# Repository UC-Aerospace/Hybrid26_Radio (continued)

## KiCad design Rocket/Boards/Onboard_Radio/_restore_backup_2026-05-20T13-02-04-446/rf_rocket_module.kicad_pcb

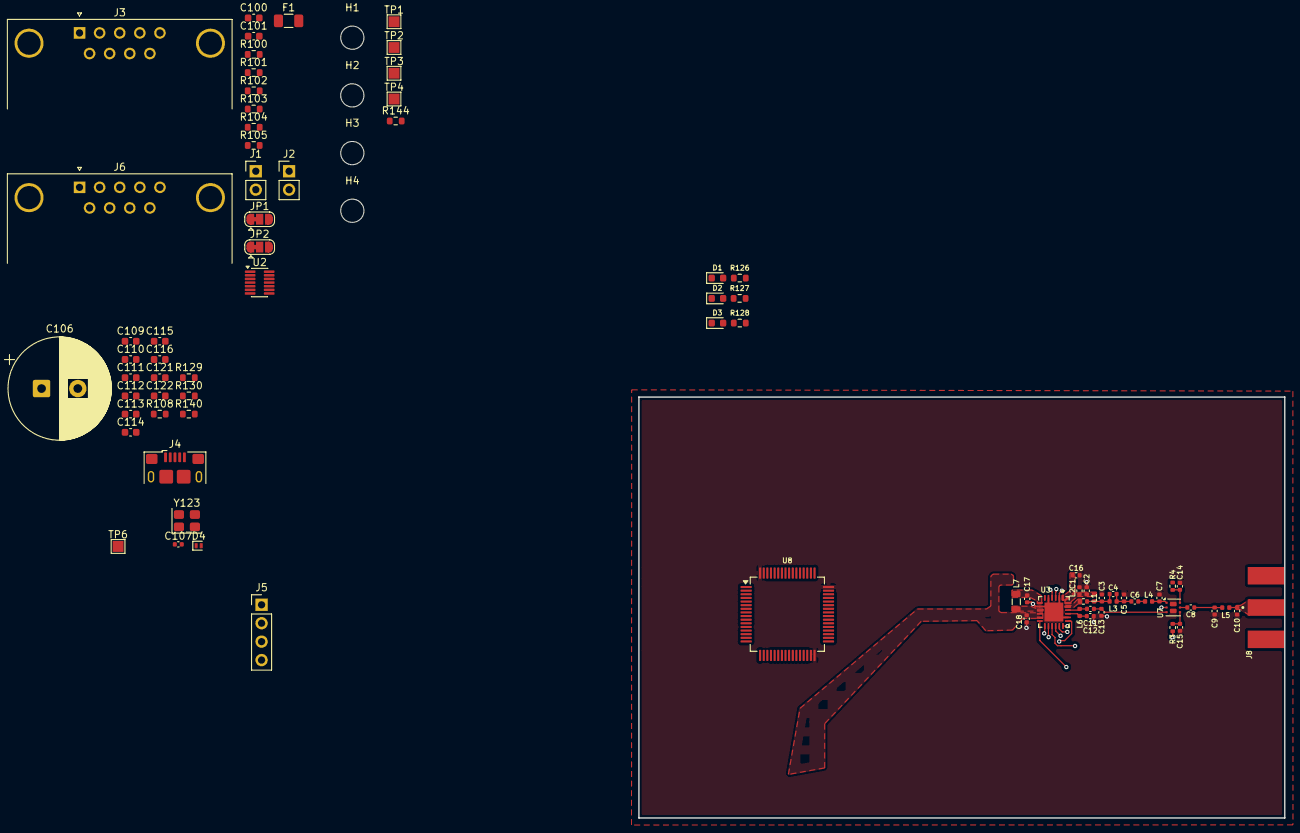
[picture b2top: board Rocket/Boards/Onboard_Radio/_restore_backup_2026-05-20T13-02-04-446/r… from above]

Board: 4 copper layers, 89.0 x 58.0 mm, 83 parts (0 on the bottom side), 53 nets.

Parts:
C1, C2: 47pF; C_0402_1005Metric
C3, C13: ???; C_0402_1005Metric
C4: 3.0pF; C_0402_1005Metric
C5: 5.6pF; C_0402_1005Metric
C6, C8: 39pF; C_0402_1005Metric
C7, C12: 1.8pF; C_0402_1005Metric
C9, C10: 3.3pF; C_0402_1005Metric
C11: 2.4pF; C_0402_1005Metric
C14, C15: 1nF; C_0402_1005Metric
C16: 1uF; C_0402_1005Metric
C17: 470nF; C_0402_1005Metric
C18: 100nF; C_0402_1005Metric
C100, C101, C109, C110, C113, C115: 100nF; C_0603_1608Metric
C106: 100m; CP_Radial_D14.0mm_P5.00mm
C107: 100n; C_0402_1005Metric
C111, C112, C114, C116: 4.7uF; C_0603_1608Metric
C121, C122: 27pF; C_0603_1608Metric
D1: LED_Y; LED_0603_1608Metric
D2: LED_G; LED_0603_1608Metric
D3: LED_R; LED_0603_1608Metric
D4: D_Schottky; D_SOD-882
F1: 5A; Fuse_1206_3216Metric
H1, H2, H3, H4: MountingHole; MountingHole_3.2mm_M3
J1: CAN1_T; PinHeader_1x02_P2.54mm_Vertical
J2: CAN2_T; PinHeader_1x02_P2.54mm_Vertical
J3, J6: DB9 Microfit; DSUB-9_Pins_Horizontal_P2.77x2.84mm_EdgePinOffset7.70mm_Hou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
J4: USB_B_Micro; USB_Micro-B_Amphenol_10118193-0001LF_Horizontal
J5: SWD JST PH; PinHeader_1x04_P2.54mm_Vertical
J8: RFIO SMA; JOHNSON_142-0701-841
JP1, JP2: CH SEL; SolderJumper-3_P1.3mm_Bridged12_RoundedPad1.0x1.5mm
L1: 47nH; L_0402_1005Metric
L2: 0R; R_0402_1005Metric
L3: 2.5nH; L_0402_1005Metric
L4: 4.7nH; L_0402_1005Metric
L5: 9.1nH; L_0402_1005Metric
L6: 15nH; L_0402_1005Metric
L7: 15uH; L_0805_2012Metric
R3, R4: 100R; R_0402_1005Metric
R100, R101, R102, R103: 100K; R_0603_1608Metric
R104, R105: 120R; R_0603_1608Metric
R108: 33R; R_0603_1608Metric
R126: 549R; R_0603_1608Metric
R127, R128: 220R; R_0603_1608Metric
R129: R; R_0603_1608Metric
R130, R140: 27R; R_0603_1608Metric
R144: 0R; R_0603_1608Metric
TP1: 7V4; TestPoint_Pad_1.5x1.5mm
TP2: 5V; TestPoint_Pad_1.5x1.5mm
TP3: 3V3; TestPoint_Pad_1.5x1.5mm
TP4: GND; TestPoint_Pad_1.5x1.5mm
TP6: RTC_CAP; TestPoint_Pad_1.5x1.5mm
U2: TCAN1046; Texas_DYY0014A_TSOT-23-14
U3: SX1262; QFN-24-1EP_4x4mm_P0.5mm_EP2.6x2.6mm
U7: PE4259 RF Switch; Vishay_PowerPAK_SC70-6L_Dual
U8: STM32H562RGT6; LQFP-64_10x10mm_P0.5mm
Y123: 12MHz; Crystal_SMD_Abracon_ABM8G-4Pin_3.2x2.5mm

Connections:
+3V3: C101.1, C109.1, C110.1, C111.1, C112.1, C113.1, C114.1, C115.1, C116.1, R100.1, R101.2, R102.2, R103.1, R108.2, R129.1, TP3.1 (1_1), U2.3 (VCC)
+5V: C100.1, TP2.1 (1_1), U2.11 (VIO)
+7V4: F1.1, R126.1, R144.2, TP1.1 (1_1)
/CAN_Termination/CAN1_RX: U2.4 (RXD1), U8.61 (PB8)
/CAN_Termination/CAN1_TX: U2.1 (TXD1), U8.59 (PB7)
/CAN_Termination/CANH: JP1.2 (C), U2.13 (CANH1)
/CAN_Termination/CANH1: J1.1, J3.6, J6.6, JP1.1 (A)
/CAN_Termination/CANH2: J3.8, J6.8, JP1.3 (B), R105.1
/CAN_Termination/CANL: JP2.2 (C), U2.12 (CANL1)
/CAN_Termination/CANL1: J3.7, J6.7, JP2.1 (A), R104.2
/CAN_Termination/CANL2: J2.1, J3.9, J6.9, JP2.3 (B)
/LoRav2/DIO2: R3.1, U3.12 (DIO2)
/MCU/LED1: R127.1, U8.9 (PC1)
/MCU/LED2: R128.1, U8.10 (PC2)
/MCU/NRST: J5.4, R129.2, U8.7 (NRST)
/MCU/SWCLK: J5.1, U8.46 (PA13(JTMS)
/MCU/SWDIO: J5.3, U8.49 (PA14(JTCK)
/MCU/USB_D+: J4.3 (D+), R140.2
/MCU/USB_D-: J4.2 (D-), R130.1
GND: C1.2, C2.2, C3.2, C5.2, C7.2, C9.2, C10.2, C12.2, C13.2, C14.2, C15.2, C16.2, C17.2, C18.2, C100.2, C101.2, C106.2, C107.2, C109.2, C110.2, C111.2, C112.2, C113.2, C114.2, C115.2, C116.2, C121.1, C122.2, D1.1 (K), D2.1 (K), D3.1 (K), J3.2, J3.4, J4.5 (GND), J5.2, J6.2, J6.4, TP4.1 (1_1), U2.2 (GND), U2.5 (GND), U3.2 (GND), U3.5 (GND), U3.8 (GND), U3.20 (GND), U3.25 (GND), U7.2 (GND), U8.12 (VSSA), U8.18 (VSS), U8.19 (VDD), U8.31 (VSS), U8.32 (VDD), U8.47 (VSS), U8.48 (VDD), U8.63 (VSS), U8.64 (VDD)
unnamed: C3.1, C4.1, L1.1, L2.2, L3.1
unnamed: C4.2, C5.1, C6.1, L3.2
unnamed: C6.2, L4.1
unnamed: C8.2, C9.1, L5.1
unnamed: D1.2 (A), R126.2
unnamed: D2.2 (A), R127.2
unnamed: D3.2 (A), R128.2
unnamed: D4.2 (A), R108.1
unnamed: C106.1, C107.1, D4.1 (K), TP6.1 (1_1), U8.1 (VBAT)
unnamed: F1.2, J3.1, J3.5, J6.1, J6.5
unnamed: J1.2, R104.1
unnamed: J2.2, R105.2
unnamed: C10.1, J8.1 (In_1), L5.2
unnamed: R102.1, U2.7 (RXD2)
unnamed: R100.2, U2.14 (STB1)
unnamed: R103.2, U2.8 (STB2)
unnamed: R101.1, U2.6 (TXD2)
unnamed: L7.1, U3.9 (DCC_SW)
unnamed: C11.1, L6.2, U3.22 (RFI_N)
unnamed: C12.1, L6.1, U3.21 (RFI_P)
unnamed: L2.1, U3.23 (RFO)
unnamed: C17.1, L7.2, U3.7 (VREG)
unnamed: C1.1, C2.1, L1.2, U3.24 (VR_PA)
unnamed: C15.1, R3.2, U7.4 (CTRL)
unnamed: C8.1, U7.5 (RFC)
unnamed: C7.1, L4.2, U7.1 (RF_1)
unnamed: C11.2, C13.1, U7.3 (RF_2)
unnamed: C14.1, R4.2, U7.6 (VDD)
unnamed: R130.2, U8.44 (PA11)
unnamed: R140.1, U8.45 (PA12)
unnamed: C121.2, U8.5 (PH0), Y123.2
unnamed: C122.1, U8.6 (PH1), Y123.1
VDD_RADIO: C16.1, C18.1, U3.1 (VDD_IN), U3.10 (VBAT), U3.11 (VBAT_IO)

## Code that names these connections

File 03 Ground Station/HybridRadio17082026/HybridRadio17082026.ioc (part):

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Mcu.Name=STM32H562RGTx
Mcu.Package=LQFP64
Mcu.UserName=STM32H562RGTx
PA0.Mode=Asynchronous
PA0.Signal=UART4_TX
PA1.Mode=Asynchronous
PA1.Signal=UART4_RX
PA11.Mode=Device
PA11.Signal=USB_DM
PA12.Mode=Device
PA12.Signal=USB_DP
PA2.GPIOParameters=GPIO_Label
PA2.GPIO_Label=ANT_SW
PA2.Signal=GPIO_Output
PA4.GPIOParameters=GPIO_Label
PA4.GPIO_Label=SX1262_CS
PA4.Signal=GPIO_Output
PA5.Mode=Full_Duplex_Master
PA5.Signal=SPI1_SCK
PA6.Mode=Full_Duplex_Master
PA6.Signal=SPI1_MISO
PA7.Mode=Full_Duplex_Master
PA7.Signal=SPI1_MOSI
PB0.GPIOParameters=GPIO_Label
PB0.GPIO_Label=SX1262_RESET
PB0.Signal=GPIO_Output
PB1.GPIOParameters=GPIO_Label
PB1.GPIO_Label=SX1262_BUSY
PB1.Signal=GPIO_Input
PB2.GPIOParameters=GPIO_Label
PB2.GPIO_Label=SX1262_DIO1
PB2.Signal=GPIO_Input
PC10.GPIOParameters=GPIO_Label
PC10.GPIO_Label=LED2
PC10.Signal=GPIO_Output
PC11.GPIOParameters=GPIO_Label
PC11.GPIO_Label=LED1
PC11.Signal=GPIO_Output
PC13.GPIOParameters=GPIO_Label
PC13.GPIO_Label=LDO_3V3A_EN
PC13.Signal=GPIO_Output
PC14-OSC32_IN(OSC32_IN).GPIOParameters=GPIO_Label
PC14-OSC32_IN(OSC32_IN).GPIO_Label=LDO_3V3D_EN
PC14-OSC32_IN(OSC32_IN).Signal=GPIO_Output
PH0-OSC_IN(PH0).Mode=HSE-External-Oscillator
PH0-OSC_IN(PH0).Signal=RCC_OSC_IN
PH1-OSC_OUT(PH1).Mode=HSE-External-Oscillator
PH1-OSC_OUT(PH1).Signal=RCC_OSC_OUT
RCC.HSE_VALUE=12000000
RCC.SYSCLKFreq_VALUE=32000000
board=custom

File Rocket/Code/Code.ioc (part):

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Mcu.Name=STM32H562RGTx
Mcu.Package=LQFP64
Mcu.UserName=STM32H562RGTx
PA11.Mode=Device
PA11.Signal=USB_DM
PA12.Mode=Device
PA12.Signal=USB_DP
PA13(JTMS/SWDIO).Mode=Serial_Wire
PA13(JTMS/SWDIO).Signal=DEBUG_JTMS-SWDIO
PA14(JTCK/SWCLK).Mode=Serial_Wire
PA14(JTCK/SWCLK).Signal=DEBUG_JTCK-SWCLK
PA4.GPIOParameters=PinState,GPIO_Label
PA4.GPIO_Label=SX1262_CS
PA4.PinState=GPIO_PIN_SET
PA4.Signal=GPIO_Output
PA5.Mode=Full_Duplex_Master
PA5.Signal=SPI1_SCK
PA6.Mode=Full_Duplex_Master
PA6.Signal=SPI1_MISO
PA7.Mode=Full_Duplex_Master
PA7.Signal=SPI1_MOSI
PB0.GPIOParameters=PinState,GPIO_Label
PB0.GPIO_Label=SX1262_RESET
PB0.PinState=GPIO_PIN_SET
PB0.Signal=GPIO_Output
PB1.GPIOParameters=GPIO_Label
PB1.GPIO_Label=SX1262_BUSY
PB1.Signal=GPIO_Output
PB2.GPIOParameters=GPIO_Label,GPIO_ModeDefaultEXTI
PB2.GPIO_Label=SX1262_DIO1
PB2.GPIO_ModeDefaultEXTI=GPIO_MODE_IT_RISING
PB2.Signal=GPXTI2
PB7.Mode=FDCAN_Activate
PB7.Signal=FDCAN1_TX
PB8.Mode=FDCAN_Activate
PB8.Signal=FDCAN1_RX
PC1.GPIOParameters=GPIO_Label
PC1.GPIO_Label=LED1
PC1.Signal=GPIO_Output
PC2.GPIOParameters=GPIO_Label
PC2.GPIO_Label=LED2
PC2.Signal=GPIO_Output
PH0-OSC_IN(PH0).Mode=HSE-External-Oscillator
PH0-OSC_IN(PH0).Signal=RCC_OSC_IN
PH1-OSC_OUT(PH1).Mode=HSE-External-Oscillator
PH1-OSC_OUT(PH1).Signal=RCC_OSC_OUT
RCC.HSE_VALUE=12000000
RCC.SYSCLKFreq_VALUE=32000000
board=custom

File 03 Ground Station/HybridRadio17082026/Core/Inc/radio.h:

/*
 * sx1262.h
 *
 * Minimal SX1262 LoRa driver for the "Onboard Radio" board.
 * Configures the radio for LoRa, -9 dBm output (the lowest the physical
 * SX1262 PA supports), 915 MHz, SF7/BW125/CR4:5, and repeatedly
 * transmits a test packet.
 *
 * All opcodes, parameter encodings, and register/pin behaviour referenced
 * against: Semtech DS.SX1261-2.W.APP Rev 1.1 ("the datasheet" in comments).
 *
 * ---- Wiring assumptions (must match your CubeMX Pinout labels) ----
 * SPI1            -> SCK/MISO/MOSI to the SX1262 (CPOL=0, CPHA=0, per
 *                    datasheet Section 8.2, p.48). NSS is software-controlled
 *                    (NOT SPI1's hardware NSS) so we can hold it low/high
 *                    exactly when the datasheet's command framing needs it.
 * SX1262_CS       -> GPIO output driving the SX1262 NSS pin
 * SX1262_BUSY     -> GPIO input reading the SX1262 BUSY pin
 * SX1262_RESET    -> GPIO output driving the SX1262 NRESET pin
 * SX1262_DIO1     -> GPIO input reading the SX1262 DIO1 pin (TxDone/Timeout IRQ)
 * LDO_3V3A_EN     -> GPIO output enabling the analog 3V3 rail that powers
 *                    the SX1262 and the PE4259 antenna switch
 * ANT_SW          -> GPIO output driving the PE4259's VDD pin (pin 6,
 *                    single-pin control mode -- held high permanently,
 *                    never toggled; CTRL (pin 4) is driven by the SX1262's
 *                    own DIO2, not by the MCU)
 *
 * Set these exact User Labels on the corresponding pins in CubeMX's
 * Pinout view so main.h generates matching SX1262_xxx_GPIO_Port/Pin macros.
 */

#ifndef SX1262_H
#define SX1262_H

#include "main.h"
#include <stdint.h>

/* Enables the analog 3V3 rail (LDO_3V3A_EN) and the PE4259 antenna
 * switch's VDD (ANT_SW), waits for the rails to settle, then runs
 * SX1262_Init(). Call once at startup, after all MX_*_Init() calls. */
HAL_StatusTypeDef Radio_PowerOn(void);

/* Initializes the radio: STDBY_RC -> LoRa packet type -> 915 MHz ->
 * PA config for lowest available power -> -9 dBm TX power -> modulation
 * params (SF7/BW125/CR4:5) -> DIO2 handed to the PE4259 antenna switch ->
 * DIO1 wired to TxDone/Timeout IRQs. Call once at startup. */
HAL_StatusTypeDef SX1262_Init(void);

/* Loads `data` (up to 255 bytes) into the TX buffer, sets the packet
 * length, transmits, and blocks until TxDone or Timeout. Returns HAL_OK
 * if TxDone fired, HAL_ERROR if a Timeout IRQ fired instead. */
HAL_StatusTypeDef SX1262_SendPacket(const uint8_t *data, uint8_t len);

#endif /* SX1262_H */

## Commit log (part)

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2026-04-29 python sim code added
2026-04-29 system architecture diagram added
2026-05-19 rf chip schematic changed
2026-05-20 schematic bom needs updating and traces need finishing
2026-05-20 pcb done, need schematic review
2026-05-20 need to finish bom
2026-05-28 can bus updeated
2026-05-28 pcb updates
2026-05-28 post narottam meetup
2026-06-02 jpole project created
2026-06-03 jpole needs review
2026-06-03 radio ic board planes joined, pcb made smaller, need to add cantraces before review
2026-06-03 schematic ready for review
2026-06-16 everything minus trace impedance and via stictching
2026-06-16 rf traces updated, need to workout board net class
2026-06-16 via fencing done, need via stiching
2026-06-17 needs pcb and schematic review
2026-06-17 updated swd and crystal
2026-06-17 jpole updates, ready for review
2026-06-18 ground station pcb and schematic created and updated
2026-06-18 via stitching added to gs board, need fencing before review
2026-06-18 file system update
2026-06-19 idk aye
2026-06-19 rocket, gs, jpole need review b4 order, update last of bom
2026-06-22 Narottam Updates Resolved
2026-06-25 radio board ordered!
